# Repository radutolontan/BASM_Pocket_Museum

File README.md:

# Introduction

The Pocket Lab is the next-generation approach to science education. Designed by the Bucharest Applied STEAM Museum, it brings scientific exploration into anyone's hands. From citizen science projects to fearless exploration (guided or individual), the Pocket Lab illuminates the connections between Science, Technology, Engineering, Art, and Math in the world around us.

---

# Hardware Design

The system is built around an **ESP32-C6 MINI** microcontroller, which offers:
- Powerful processing capabilities
- WiFi and Bluetooth connectivity
- Excellent integration with accessible codebases through Arduino

The microcontroller collects data from a suite of sensors (9-DOF IMU, light, pressure, audio) and uses a chain of WS2812B RGB LEDs to relay measurements to the user. An on-board microSD card enables data logging and automated grading of student work. Everything is powered by a 3.7V LiPo cell, which is charged using the USB-C connector.
## Board ID - Education V0

### Power
The power stage is designed for a **500 mAh, 3.7V LiPo cell**. Key specifications:
- **Charger IC**: Configured to supply 450 mA in constant-current regime; stops charging when current drops below 150 mA in constant-voltage regime
- **USB-C Power**: Non-negotiated supply limited to 5V @ 500 mA (sufficient for system operation)
- **Voltage Monitor**: Prevents brown-out behavior on the ESP32 when the 3.3V rail drops below 2.9V
- **Power Latching**: A simple circuit enables and latches the LDO through push-button SW1 and an ESP32 GPIO 

### Display
The display consists of a chain of NeoPixel RGB LEDs organized across three zones:

**Mode Display (2 LEDs)** - Color-coded indication of the actively displayed quantity:
- WHITE → Light
- MAGENTA → Sound
- YELLOW → Magnetic Field
- GREEN → Acceleration
- ORANGE → Gyroscope
- RED → Air Temperature
- BLUE → Air Pressure

Additional device information is also displayed (e.g., battery state: Blinking Orange = Battery Low; Blinking Green = Charging; Blinking Blue = Fully Charged)

**Magnitude Display (3-4 LEDs)** - Conveys scalar quantities and magnitudes of vector quantities

**Direction Display (3 LEDs)** - Conveys qualitative Cartesian components (X, Y, Z) for vector quantities
- *Note: Direction Display is only available in Binary Display Mode (see Software Architecture section)*

### Sensors
The Pocket Lab EDU V0 includes the following sensors:

| Sensor | Measurements |
|--------|-------------|
| **ICM-20948** | 9-DOF IMU: translational acceleration, rotational velocity, magnetic field strength |
| **ICP-20100** | Ambient temperature and air pressure |
| **BH1750FVI** | Ambient light intensity |
| **MMICT390200012** | Microphone: sound pressure level (dB) |

### Programming
The MCU can be programmed through **Joint Download Boot Mode**:

1. Connect the Pocket Lab to a host computer using a USB-C data cable
2. Hold down **SW2** (labeled "MOD"; connected to GPIO 9)
3. While holding SW2, press and hold **SW1** (labeled "ON/OFF")
4. Release SW2 while keeping SW1 pressed
5. Release SW1

The USB-serial connection appears as `/dev/ttyACM*` (Linux) and allows PlatformIO to flash code to the ESP32-C6.

# Software Architecture

The software architecture is built around a FreeRTOS task-based design with a central `shared_data_buffer` for inter-task communication. Tasks are organized into two tiers:

## Task Organization

### First-Tier Tasks (Core System)
These tasks are **always active** and form the foundation of the Pocket Lab operation:
- **BMSTask** - Battery management and power control
- **SensorTask** - Sensor data acquisition and processing
- **AudioTask** - Audio input/output management
- **DisplayTask** - User interface via NeoPixel LEDs

### Application-Level Tasks (Feature-Specific)
These tasks are **conditionally enabled** based on active applications, demos, or features:
- **SDManager** - MicroSD card operations for data logging
- **EvaluatorTask** - Student performance assessment and grading
- **NetworkTask** - WiFi/Bluetooth connectivity features

## System Architecture Diagram

```mermaid
graph TB
    subgraph "First-Tier Tasks"
        BMS[BMSTask<br/>Power Management]
        SENSOR[SensorTask<br/>Data Acquisition]
        AUDIO[AudioTask<br/>Audio I/O]
        DISPLAY[DisplayTask<br/>Visual Feedback]
    end

    subgraph "Shared Memory"
        BUFFER[(SharedBuffer<br/>Circular Buffer)]
    end

    subgraph "Application Tasks"
        SD[SDManager]
        EVAL[EvaluatorTask]
        NET[NetworkTask]
    end

    BMS -->|Power Status| BUFFER
    SENSOR -->|Sensor Data| BUFFER
    AUDIO -->|Audio Data| BUFFER

    BUFFER -->|Latest Data| DISPLAY
    BUFFER -->|Historical Data| SD
    BUFFER -->|Statistics| EVAL
    BUFFER -->|Stream Data| NET

    BMS -.->|Shutdown Signal| SENSOR
    BMS -.->|Shutdown Signal| AUDIO
    BMS -.->|Shutdown Signal| DISPLAY

    DISPLAY -->|Mode Changes| BUFFER

    style BMS fill:#ffcccc
    style SENSOR fill:#ccffcc
    style AUDIO fill:#ccccff
    style DISPLAY fill:#ffffcc
    style BUFFER fill:#ffccff
```

## Detailed Task Descriptions
### 1. SensorTask
Responsible for initializing, managing, collecting, and processing sensor data. Pushes each new raw reading to the `shared_data_buffer`. Uses the **SensorHAL** virtual layer, as implemented in `specific_sensor_HAL`, to standardize high-level I/O across all sensors.

Furthermore, note that different sensors are sampled at different rates based on their response characteristics and application requirements.
The task maintains individual timers for each sensor and only reads when that sensor's interval has elapsed, optimizing power consumption and computational load.

#### States
* **BOOT** - Default state on boot-up; transition to INIT triggered from main.cpp
* **INIT** - Initializes I2C bus for communications to sensors, configures and confirms communications with all sensors
* **READ** - If a sensor is ready to read (based on its individual `read_rate_Hz`), captures a raw reading and commits it to the latest frame of `shared_data_buffer`

### 2. BMSTask
Responsible for managing power delivery to the Pocket Lab. Monitors battery health, informs user about remaining run-time, and handles power-up and shut-down of the entire system.

#### States
* **BOOT** - Waits until startup timer expires. Prevents accidental power-up if SW 1 is bumped.
* **STARTUP_LATCH** - Configures Charger IC monitoring pins after confirming power is latched.
* **ACTIVE** - Monitors feedback from the Charger IC & Battery Voltage predictions to infer ChargeControllerState:
    * **BATTERY_ONLY** - Charger unplugged & battery supplying power
    * **LOW_BATTERY** - Charger unplugged & battery supplying power & less than 30 minutes of battery life remaining
    * **CHARGING** - Charger connected & battery charging
    * **DONE_CHARGING** - Charger connected & supplying power to system (battery charging complete)
* **SHUTDOWN_PENDING** - When SW 1 is pressed to initiate a shut-down, the LDO is un-latched and other tasks are informed to facilitate a clean shut-down.

#### ⚠️ Known Critical Issues
The current BMSTask implementation has several critical issues that will be addressed in future revisions:
- **Limited voltage monitoring**: VBat is only checked when in `BATTERY_ONLY` state, missing voltage drops during charging or when connected to USB
- **No automatic low-voltage disconnect**: The system does not automatically disconnect power when VBat drops dangerously low, risking deep discharge that could trigger the battery's undervoltage lockout protection

### 3. AudioTask
Manages audio input and output operations for the Pocket Lab. The AudioTask is responsible for interfacing with the microphone sensor (MMICT390200012) and any future audio peripherals through a Hardware Abstraction Layer (HAL).
This decouples high-level audio processing from hardware-specific implementations, allowing to scale audio I/O in the future.
Like the SensorTask, the AudioTask writes processed audio data (e.g., sound pressure level in dB, frequency analysis) to the `shared_data_buffer`.

#### States
* **BOOT** - Default state on boot-up; transition to INIT triggered from main.cpp
* **INIT** - Initializes audio peripherals through the AudioHAL, configures sampling parameters
* **SAMPLING** - Actively captures audio data at the configured sample rate, processes it, and commits results to `shared_data_buffer`
* **IDLE** - Audio acquisition paused (e.g., during low-power modes or when no audio display is active)

### 4. DisplayTask
Manages the primary user feedback tool, the chain of NeoPixels. A push-button (SW 2 - display mode button) is debounced and used to cycle through DisplayStates. The current DisplayState is color-coded into the **Mode Display**.

#### States
* **BOOT** - Default state on boot-up; transition to INIT triggered from main.cpp
* **INIT** - Initializes the RGB LED strip and displays a color code for the GIT SHA (used to confirm proper code version is running)
* **DISPLAY_XX** - Pulls the latest value for the XX quantity from `shared_data_buffer`. Updates the **Magnitude Display** and **Mode Display** to reflect the measurement.

The DisplayTask supports two distinct visualization modes selected at boot time by holding (or not holding) the display mode button:

#### Visualization Modes - VU

VU mode provides a classic "volume unit" meter visualization reminiscent of analog audio equipment. In this mode, scalar measurements are displayed as a horizontal bar graph using 6 magnitude LEDs. The display shows the normalized percentage of the measurement relative to predefined min/max thresholds for each sensor type.

The magnitude LEDs use a gradient color scheme that transitions smoothly from green (low values) through yellow (mid-range) to red (high values), providing an intuitive visual indication of intensity. The more LEDs that are lit, the closer the measurement is to its maximum threshold. Vector quantities in VU mode display only their magnitude - no directional information is shown.

#### Visualization Modes - Binary (Integer Encoding)

Binary mode takes a fundamentally different approach by encoding the actual integer value of measurements rather than showing a percentage. This mode provides precise numerical information that can be decoded by reading the LED colors, making it particularly useful for debugging and data verification.

The system uses 4 magnitude LEDs to encode 12-bit values (0-4095) using a novel 3-bit-per-LED color encoding scheme:

**How Binary Encoding Works:**

Each RGB LED encodes 3 bits of information using its individual color channels:
- Blue channel = Bit m (LSB for that LED)
- Yellow channel = Bit m+1 (middle bit)
- Red channel = Bit m+2 (MSB for that LED)

The LEDs are arranged from left to right, with LED #1 (leftmost) showing bits 0-2, LED #2 showing bits 3-5, LED #3 showing bits 6-8, and LED #4 (rightmost) showing bits 9-11. This arrangement means that more LEDs being lit indicates a larger magnitude.

**Color Combinations:** The 3 bits per LED create 8 possible states (0-7), each displayed as a distinct color:
- `000` → OFF
- `001` → BLUE (bit 0 only)
- `010` → YELLOW (bit 1 only)
- `011` → GREEN (bits 0+1: blue+yellow = green)
- `100` → RED (bit 2 only)
- `101` → PURPLE (bits 0+2: blue+red = purple)
- `110` → ORANGE (bits 1+2: yellow+red = orange)
- `111` → WHITE (all three bits active)

**Example:** To encode the value 1059:
- 1059 in binary = `0100 0010 0011` = 2⁰ + 2¹ + 2⁵ + 2¹⁰
- LED #1 (bits 0-2 = `011`): Blue + Yellow = **GREEN**
- LED #2 (bits 3-5 = `100`): Red only = **RED**
- LED #3 (bits 6-8 = `000`): All off = **OFF**
- LED #4 (bits 9-11 = `100`): Red only = **RED**

Before encoding, sensor readings are multiplied by sensor-specific scaling factors (defined as `BINARY_MAG_ORDER_*` constants) to convert floating-point measurements into integer values. For example, temperature is multiplied by 10, so 25.3°C becomes 253, while pressure is multiplied by 10, converting 101.32 kPa to 1013 (then clamped to 4095). Note that acceleration and gyro measurements are very noisy and flicker significantly; the first two bits are masked, effectively rounding every measurement to a multiple of 4.

**Direction Display:**

Binary mode also displays vector components (X, Y, Z) using 3 dedicated direction LEDs. Each LED shows its component using a color gradient:
- **RED** → Negative values
- **OFF** → Near-zero values (±5% dead zone)
- **GREEN** → Positive values

The intensity of the color fades proportionally with the component's magnitude, providing both sign and strength information. 

## Application-Level Task Details

### 5. EvaluatorTask
Responsible for gauging user effort and measuring learning outcomes. The EvaluatorTask owns multiple instances of the abstract base class `EvaluatorBase`.

`EvaluatorBase` standardizes I/O across all evaluators, such as `DisplaySessionEvaluator` (which captures aggregate statistics on sensor data while a specific DisplayTask mode is active). This enables automated grading and feedback for educational activities.

#### States
* **BOOT** - Default state on boot-up; transition to INIT triggered from main.cpp
* **INIT** - Initializes and confirms appropriate logging is set up for all evaluators
* **RUNNING** - Checks progress on all evaluators and manages access to the SDManager queue for data logging
* **ERROR** - Error handling (not yet implemented)

### 6. SDManager
Owns operation of the microSD card. It manages access to the storage resource using a separate state machine, handling concurrent read/write requests from multiple tasks.

#### States
* **BOOT** - Default state on boot-up; transitions to INIT automatically after initializing SD queue
* **WAIT_FOR_INSERT** - Checks and debounces the state of the SD card detect GPIO
* **MOUNTING** - Starts SPI communications, mounts the SD card, and checks SD card metadata
* **READY** - Allows fulfillment of read/write requests in the queue
* **UNMOUNTING** - Unmounts the SD card if removal is detected
* **ERROR** - Error handling (not yet implemented)

### 7. NetworkTask
Manages WiFi and Bluetooth connectivity features. This task is enabled when network-based applications are active (e.g., data streaming, remote monitoring, firmware updates).

*Note: Full NetworkTask implementation details are under development.*

---

# SD Card Formatting

In order to read and write to the SD card, it must be formatted to **FAT32** with an **MBR** partition table.

## Formatting Instructions (Linux)

1. Insert the microSD card into a compatible card reader, connect to a Linux machine, and locate the device:
```bash
lsblk
```

2. Unmount any existing partitions and clear the card (replace `/dev/sdX` with your device):
```bash
sudo umount /dev/sdX*
sudo wipefs --all /dev/sdX
sudo fdisk /dev/sdX
```

3. Within `fdisk`, configure the following:
   - Press **`o`** → Create a new DOS (MBR) partition table
   - Press **`n`** → Create a new primary partition
   - Accept all defaults (press Enter)
   - Press **`t`**, then type **`c`** → Change partition type to W95 FAT32 (LBA)
   - Press **`w`** → Write changes and exit

4. Format the partition to FAT32:
```bash
sudo mkfs.vfat -F 32 -n SDCARD /dev/sdX1
```

The SD card is now ready for use with the Pocket Lab.

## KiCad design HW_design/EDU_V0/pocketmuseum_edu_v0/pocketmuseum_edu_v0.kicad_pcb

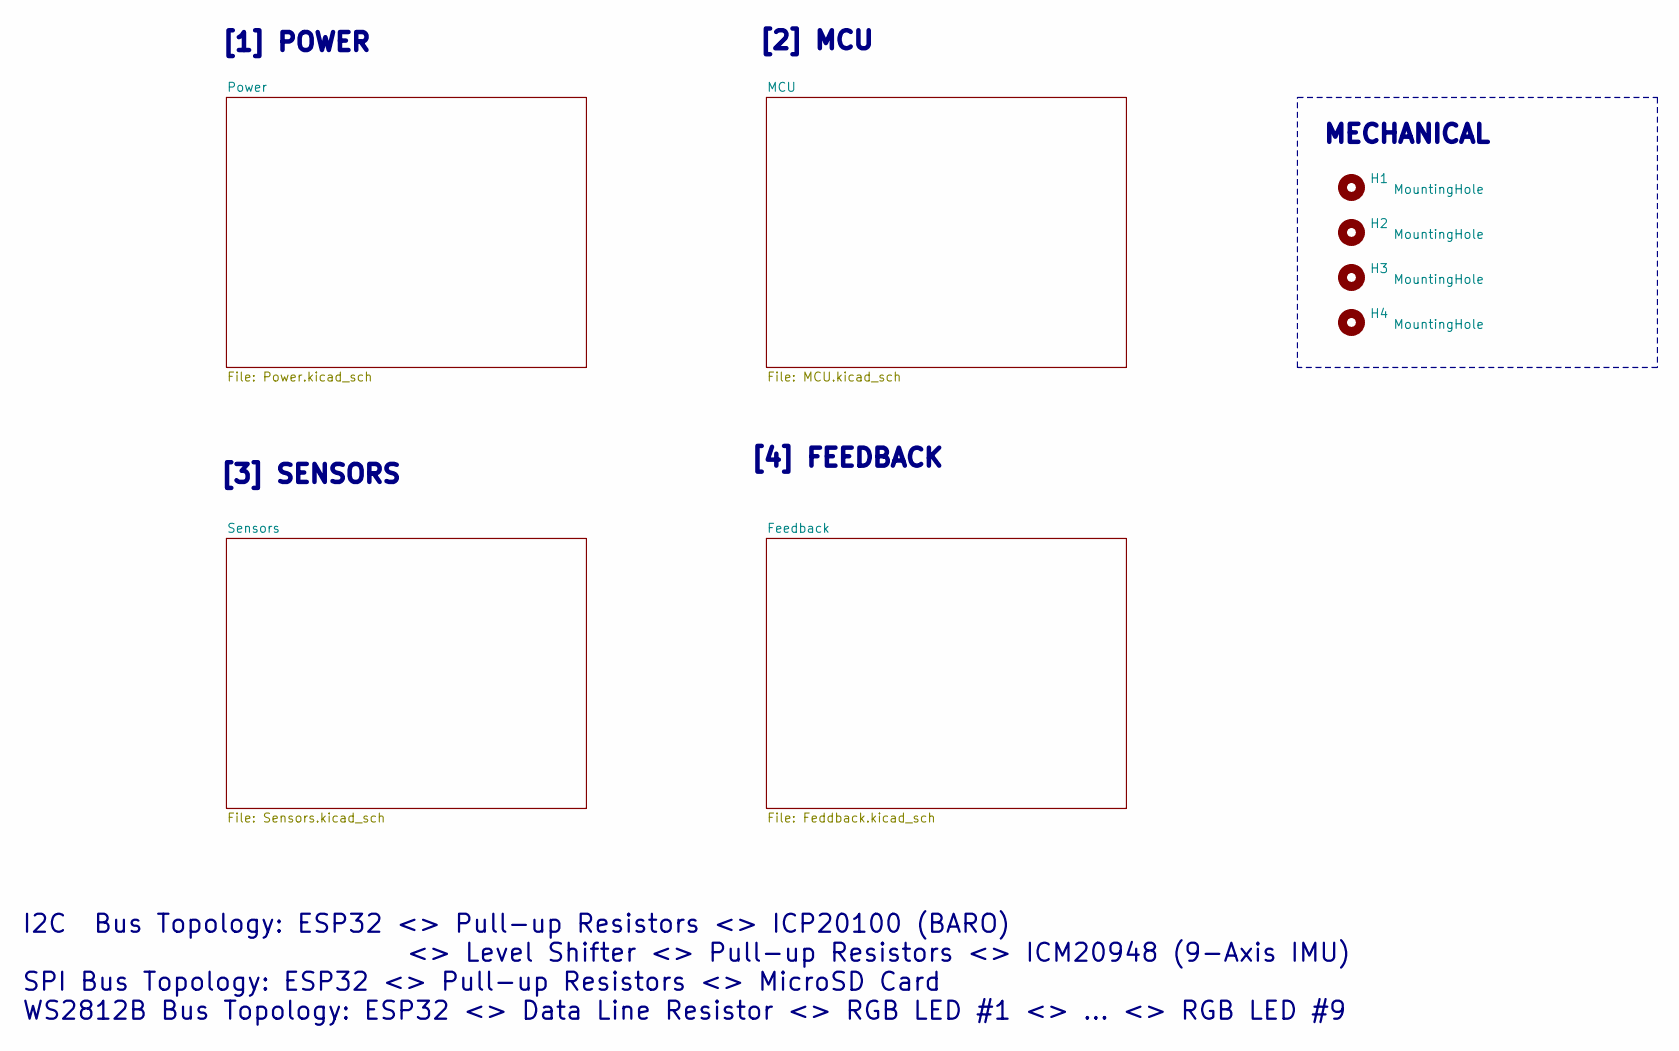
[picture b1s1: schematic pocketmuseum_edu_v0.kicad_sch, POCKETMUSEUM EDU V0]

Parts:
H1, H2, H3, H4: MountingHole; MountingHole_3.2mm_M3

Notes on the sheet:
[1] POWER
I2C Bus Topology: ESP32 <> Pull-up Resistors <> ICP20100 (BARO) <> Level Shifter <> Pull-up Resistors <> ICM20948 (9-Axis IMU) SPI Bus Topology: ESP32 <> Pull-up Resistors <> MicroSD Card WS2812B Bus Topology: ESP32 <> Data Line Resistor <> RGB LED #1 <> ... <> RGB LED #9
[2] MCU
[3] SENSORS
MECHANICAL
[4] FEEDBACK

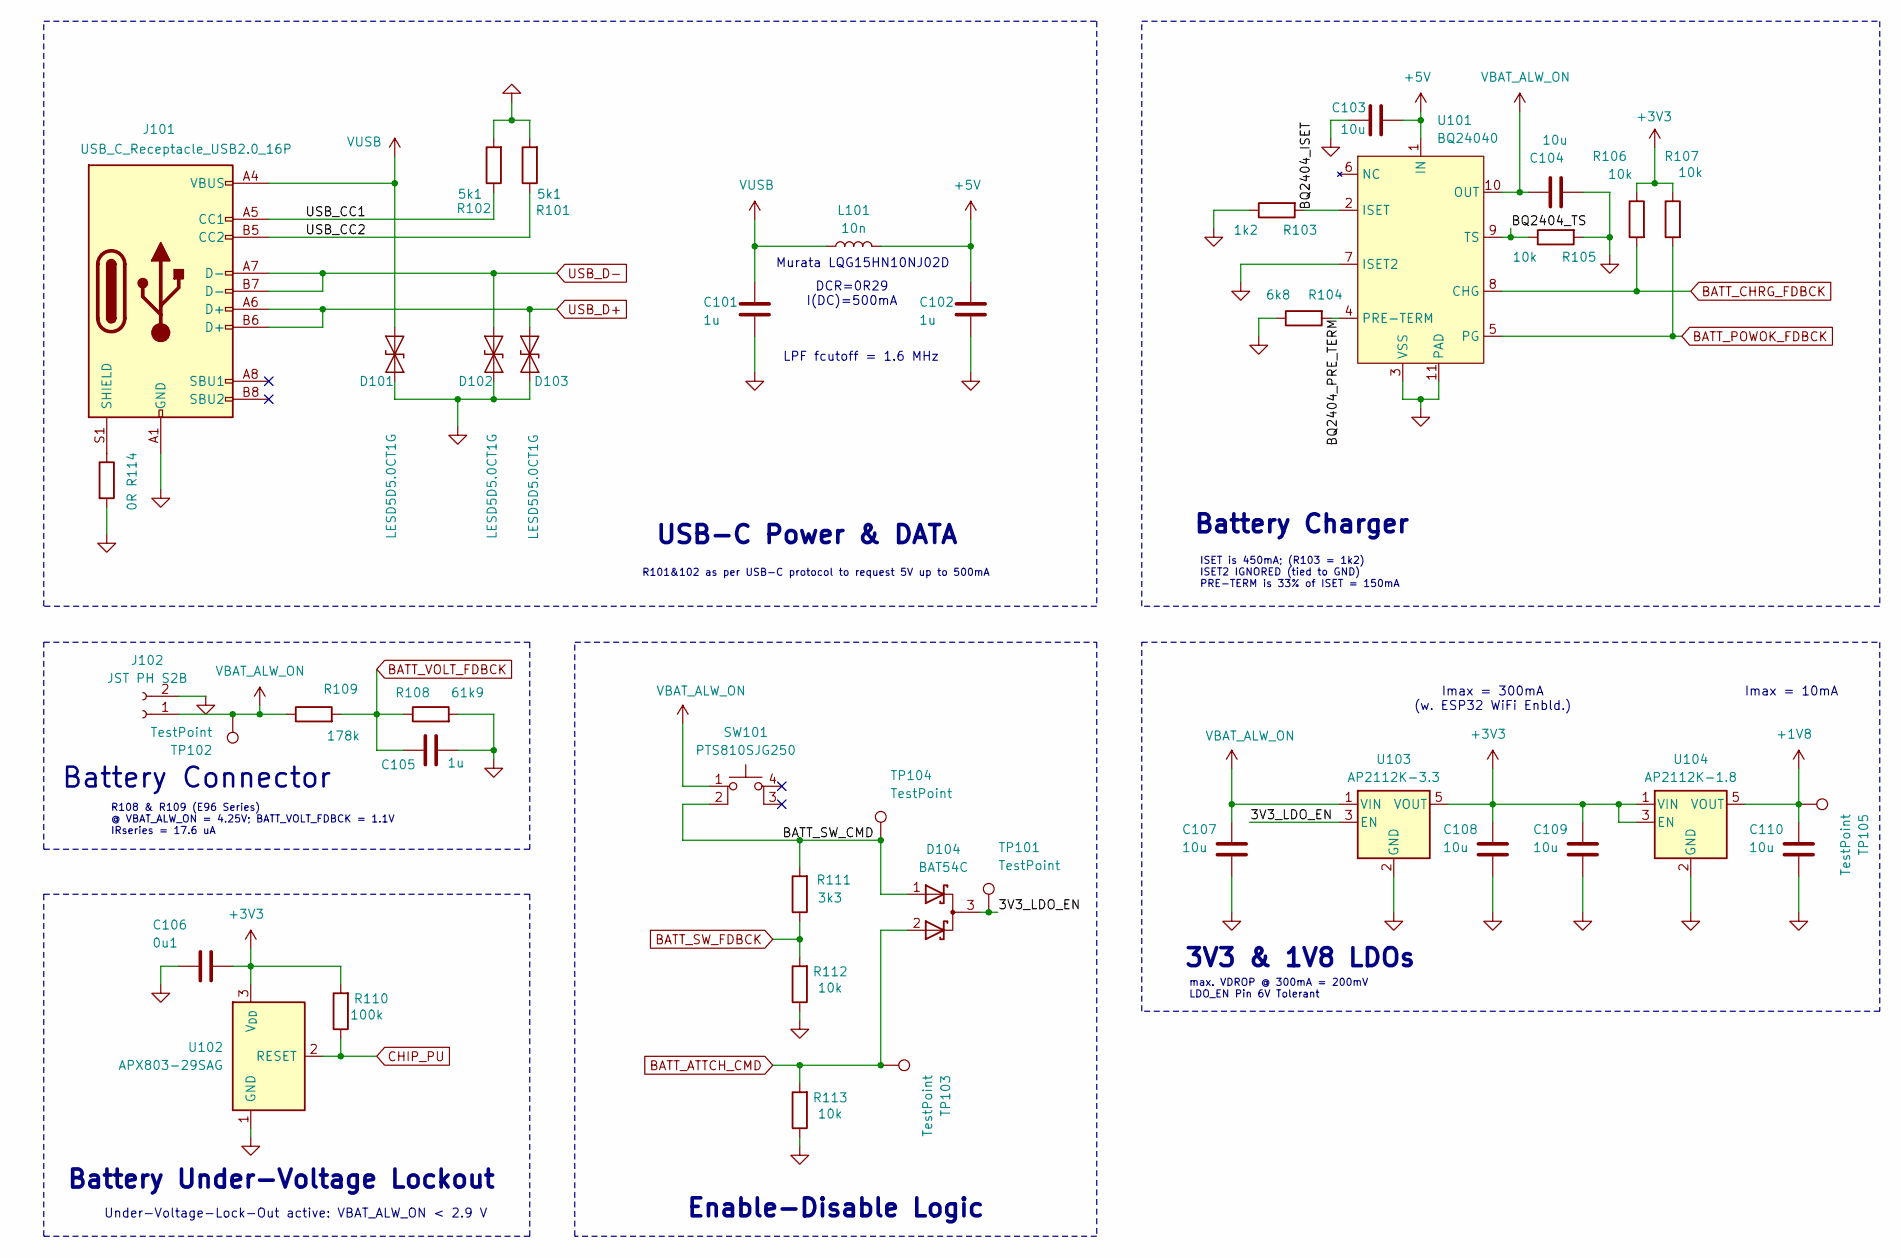
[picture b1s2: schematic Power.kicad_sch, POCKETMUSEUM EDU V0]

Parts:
C101, C102, C105: 1u; C_0402_1005Metric; Manufacturer P/N CL05A105KP5NNNC
C103, C104: 10u; C_0603_1608Metric; Manufacturer P/N CL05A105KP5NNNC
C106: 0u1; C_0402_1005Metric; Manufacturer P/N CL05A105KP5NNNC
C107, C108, C109, C110: 10u; C_0603_1608Metric; Manufacturer P/N CL10A226MQ8NRNC
D101, D102, D103: LESD5D5.0CT1G; D_SOD-523; Manufacturer P/N LESD5D5.0CT1G
D104: BAT54C; SOT-23
J101: USB_C_Receptacle_USB2.0_16P; USB_C_Receptacle_HRO_TYPE-C-31-M-12; Manufacturer P/N TYPE-C-31-M-12
J102: JST PH S2B; JST_PH_S2B-PH-SM4-TB_1x02-1MP_P2.00mm_Horizontal
L101: 10n; L_0402_1005Metric; Manufacturer P/N LQG15HS10NJ02D
R101, R102: 5k1; R_0402_1005Metric; Manufacturer P/N 0402WGF5101TCE
R103: 1k2; R_0402_1005Metric; Manufacturer P/N 0402WGF5101TCE
R104: 6k8; R_0402_1005Metric; Manufacturer P/N 0402WGF5101TCE
R105, R106, R107, R112, R113: 10k; R_0402_1005Metric; Manufacturer P/N 0402WGF5101TCE
R108: 61k9; R_0402_1005Metric; Manufacturer P/N 0402WGF5101TCE
R109: 178k; R_0402_1005Metric; Manufacturer P/N 0402WGF5101TCE
R110: 100k; R_0402_1005Metric; Manufacturer P/N 0402WGF5101TCE
R111: 3k3; R_0402_1005Metric; Manufacturer P/N 0402WGF5101TCE
R114: 0R; R_0603_1608Metric; Manufacturer P/N 0603WAJ0000T5E
SW101: PTS810SJG250; SW_SPST_PTS810
TP101, TP102, TP103, TP104, TP105: TestPoint; TestPoint_Pad_D2.0mm
U101: BQ24040; QFN_10_BQ24040
U102: APX803-29SAG; SOT-23
U103: AP2112K-3.3; SOT-23-5
U104: AP2112K-1.8; SOT-23-5

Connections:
+1V8: C110.1, TP105.1, U104.5 (VOUT); also elsewhere on the board
+3V3: C106.1, C108.1, C109.1, R106.1, R107.1, R110.2, U102.3 (V_{DD}), U103.5 (VOUT), U104.1 (VIN), U104.3 (EN); also elsewhere on the board
+5V: C102.1, C103.1, L101.2, U101.1 (IN)
/Power/3V3_LDO_EN: D104.3 (K), TP101.1, U103.3 (EN)
/Power/BATT_SW_CMD: D104.1 (A), R111.2, SW101.2, TP104.1
/Power/BQ2404_ISET: R103.2, U101.2 (ISET)
/Power/BQ2404_PRE_TERM: R104.2, U101.4 (PRE-TERM)
/Power/BQ2404_TS: R105.1, U101.9 (TS)
/Power/USB_CC1: J101.A5 (CC1), R102.1
/Power/USB_CC2: J101.B5 (CC2), R101.1
BATT_ATTCH_CMD: D104.2 (A), R113.2, TP103.1; also elsewhere on the board
BATT_CHRG_FDBCK: R106.2, U101.8 (CHG); also elsewhere on the board
BATT_POWOK_FDBCK: R107.2, U101.5 (PG); also elsewhere on the board
BATT_SW_FDBCK: R111.1, R112.2; also elsewhere on the board
BATT_VOLT_FDBCK: C105.1, R108.1, R109.2; also elsewhere on the board
CHIP_PU: R110.1, U102.2 (RESET); also elsewhere on the board
GND: C101.2, C102.2, C103.2, C104.2, C105.2, C106.2, C107.2, C108.2, C109.2, C110.2, D101.2 (A2), D102.2 (A2), D103.1 (A1), J101.A1 (GND), J101.A12 (GND), J101.B1 (GND), J101.B12 (GND), J102.2, R101.2, R102.2, R103.1, R104.1, R105.2, R108.2, R112.1, R113.1, R114.2, U101.3 (VSS), U101.7 (ISET2), U101.11 (PAD), U102.1 (GND), U103.2 (GND), U104.2 (GND); also elsewhere on the board
unnamed: J101.S1 (SHIELD), R114.1
USB_D+: D103.2 (A2), J101.A6 (D+), J101.B6 (D+); also elsewhere on the board
USB_D-: D102.1 (A1), J101.A7 (D-), J101.B7 (D-); also elsewhere on the board
VBAT_ALW_ON: C104.1, C107.1, J102.1, R109.1, SW101.1, TP102.1, U101.10 (OUT), U103.1 (VIN)
VUSB: C101.1, D101.1 (A1), J101.A4 (VBUS), J101.A9 (VBUS), J101.B4 (VBUS), J101.B9 (VBUS), L101.1

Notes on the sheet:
Murata LQG15HN10NJ02D
Under-Voltage-Lock-Out active: VBAT_ALW_ON < 2.9 V
Battery Connector
Imax = 300mA (w. ESP32 WiFi Enbld.)
ISET is 450mA; (R103 = 1k2) ISET2 IGNORED (tied to GND) PRE-TERM is 33% of ISET = 150mA
Battery Charger
DCR=0R29 I(DC)=500mA
USB-C Power & DATA
Battery Under-Voltage Lockout
R108 & R109 (E96 Series) @ VBAT_ALW_ON = 4.25V; BATT_VOLT_FDBCK = 1.1V IRseries = 17.6 uA
Enable-Disable Logic
max. VDROP @ 300mA = 200mV LDO_EN Pin 6V Tolerant
Imax = 10mA
LPF fcutoff = 1.6 MHz
3V3 & 1V8 LDOs
R101&102 as per USB-C protocol to request 5V up to 500mA

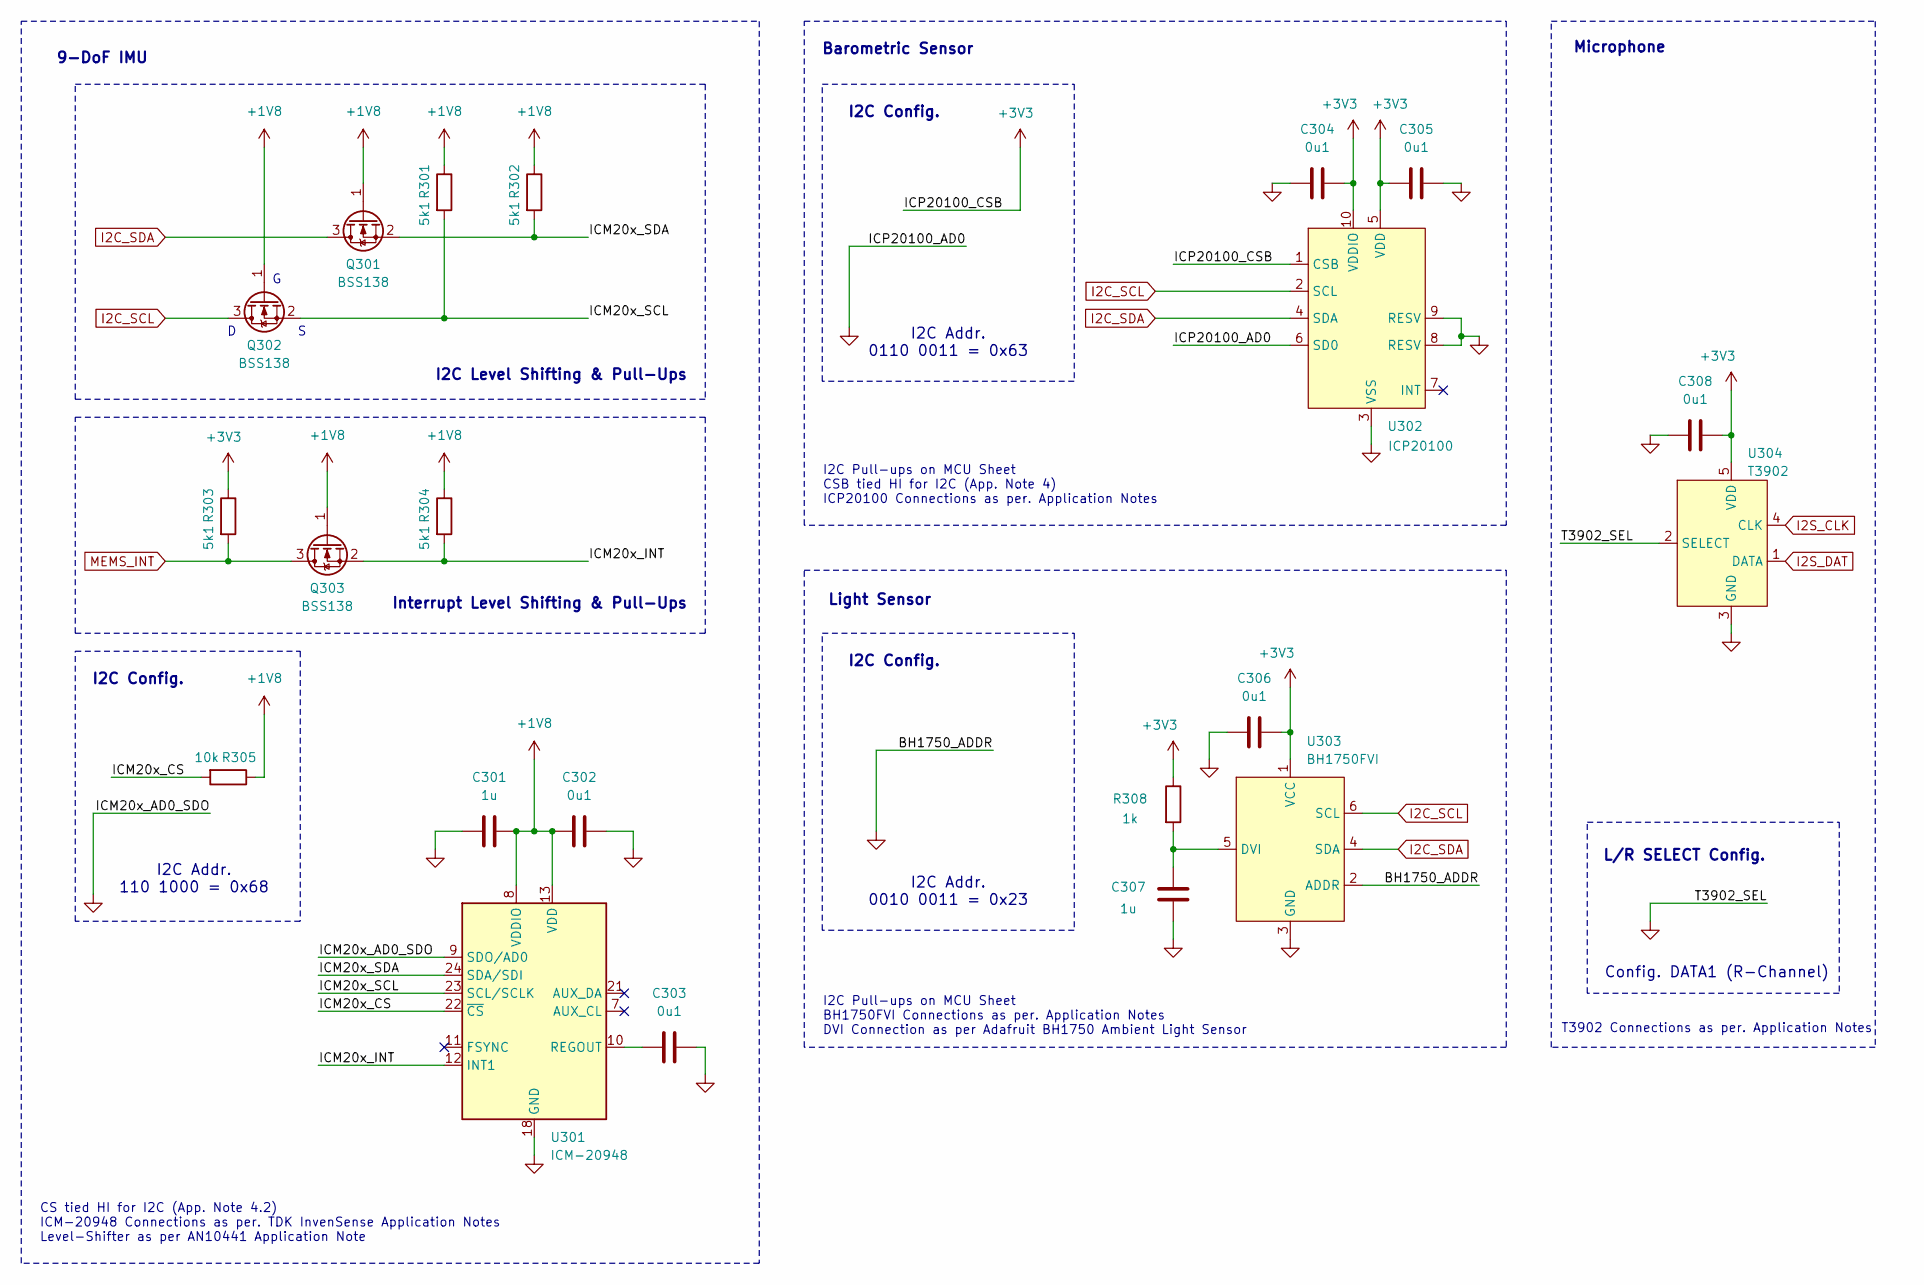
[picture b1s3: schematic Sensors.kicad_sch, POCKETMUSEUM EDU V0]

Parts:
C301, C307: 1u; C_0402_1005Metric; Manufacturer P/N CL05B104KO5NNNC
C302, C303, C304, C305, C306, C308: 0u1; C_0402_1005Metric; Manufacturer P/N CL05B104KO5NNNC
Q301, Q302, Q303: BSS138; SOT-23
R301, R302, R303, R304: 5k1; R_0402_1005Metric; Manufacturer P/N 0603WAJ0000T5E
R305: 10k; R_0402_1005Metric; Manufacturer P/N 0603WAJ0000T5E
R308: 1k; R_0402_1005Metric; Manufacturer P/N 0603WAJ0000T5E
U301: ICM-20948; InvenSense_QFN-24_3x3mm_P0.4mm
U302: ICP20100; ST_HLGA-10_2x2mm_P0.5mm_LayoutBorder3x2y; Manufacturer P/N ICP-20100
U303: BH1750FVI; XDCR_BH1750FVI-TR
U304: T3902; MMIC

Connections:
+1V8: C301.1, C302.2, Q301.1 (G), Q302.1 (G), Q303.1 (G), R301.1, R302.1, R304.1, R305.1, U301.8 (VDDIO), U301.13 (VDD); also elsewhere on the board
+3V3: C304.1, C305.2, C306.1, C308.1, R303.1, R308.1, U302.1 (CSB), U302.5 (VDD), U302.10 (VDDIO), U303.1 (VCC), U304.5 (VDD); also elsewhere on the board
/Sensors/ICM20x_CS: R305.2, U301.22 (~CS)
/Sensors/ICM20x_INT: Q303.2 (S), R304.2, U301.12 (INT1)
/Sensors/ICM20x_SCL: Q302.2 (S), R301.2, U301.23 (SCL/SCLK)
/Sensors/ICM20x_SDA: Q301.2 (S), R302.2, U301.24 (SDA/SDI)
GND: C301.2, C302.1, C303.1, C304.2, C305.1, C306.2, C307.2, C308.2, U301.9 (SDO/AD0), U301.18 (GND), U301.20 (GND), U302.3 (VSS), U302.6 (SD0), U302.8 (RESV), U302.9 (RESV), U303.2 (ADDR), U303.3 (GND), U304.2 (SELECT), U304.3 (GND); also elsewhere on the board
I2C_SCL: Q302.3 (D), U302.2 (SCL), U303.6 (SCL); also elsewhere on the board
I2C_SDA: Q301.3 (D), U302.4 (SDA), U303.4 (SDA); also elsewhere on the board
I2S_CLK: U304.4 (CLK); also elsewhere on the board
I2S_DAT: U304.1 (DATA); also elsewhere on the board
MEMS_INT: Q303.3 (D), R303.2; also elsewhere on the board
unnamed: C303.2, U301.10 (REGOUT)
unnamed: C307.1, R308.2, U303.5 (DVI)

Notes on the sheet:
I2C Pull-ups on MCU Sheet BH1750FVI Connections as per. Application Notes DVI Connection as per Adafruit BH1750 Ambient Light Sensor
I2C Pull-ups on MCU Sheet CSB tied HI for I2C (App. Note 4) ICP20100 Connections as per. Application Notes
T3902 Connections as per. Application Notes
I2C Config.
Microphone
I2C Addr. 0110 0011 = 0x63
I2C Addr. 110 1000 = 0x68
I2C Addr. 0010 0011 = 0x23
9-DoF IMU
Config. DATA1 (R-Channel)
Light Sensor
CS tied HI for I2C (App. Note 4.2) ICM-20948 Connections as per. TDK InvenSense Application Notes Level-Shifter as per AN10441 Application Note
I2C Level Shifting & Pull-Ups
Barometric Sensor
L/R SELECT Config.
Interrupt Level Shifting & Pull-Ups

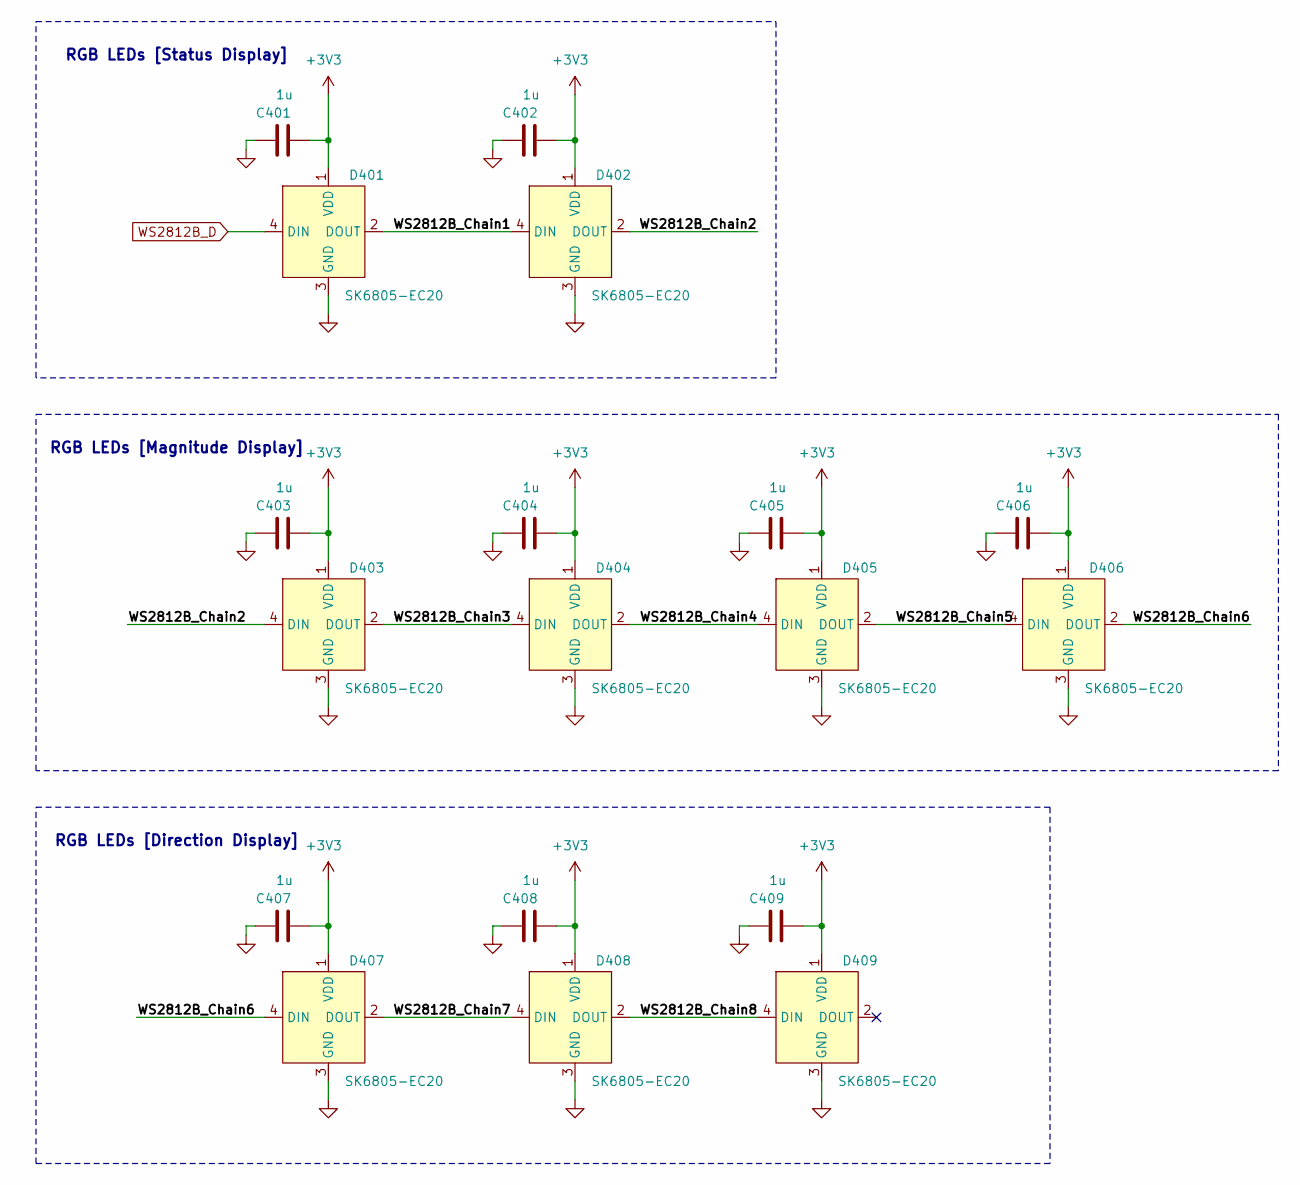
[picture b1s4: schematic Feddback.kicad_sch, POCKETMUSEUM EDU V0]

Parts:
C401, C402, C403, C404, C405, C406, C407, C408, C409: 1u; C_0402_1005Metric; Manufacturer P/N CL05A105KP5NNNC
D401, D402, D403, D404, D405, D406, D407, D408, D409: SK6805-EC20; SK68xx-EC20; Manufacturer P/N SK6805-EC20

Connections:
+3V3: C401.2, C402.2, C403.2, C404.2, C405.2, C406.2, C407.2, C408.2, C409.2, D401.1 (VDD), D402.1 (VDD), D403.1 (VDD), D404.1 (VDD), D405.1 (VDD), D406.1 (VDD), D407.1 (VDD), D408.1 (VDD), D409.1 (VDD); also elsewhere on the board
/Feedback/WS2812B_Chain1: D401.2 (DOUT), D402.4 (DIN)
/Feedback/WS2812B_Chain2: D402.2 (DOUT), D403.4 (DIN)
/Feedback/WS2812B_Chain3: D403.2 (DOUT), D404.4 (DIN)
/Feedback/WS2812B_Chain4: D404.2 (DOUT), D405.4 (DIN)
/Feedback/WS2812B_Chain5: D405.2 (DOUT), D406.4 (DIN)
/Feedback/WS2812B_Chain6: D406.2 (DOUT), D407.4 (DIN)
/Feedback/WS2812B_Chain7: D407.2 (DOUT), D408.4 (DIN)
/Feedback/WS2812B_Chain8: D408.2 (DOUT), D409.4 (DIN)
GND: C401.1, C402.1, C403.1, C404.1, C405.1, C406.1, C407.1, C408.1, C409.1, D401.3 (GND), D402.3 (GND), D403.3 (GND), D404.3 (GND), D405.3 (GND), D406.3 (GND), D407.3 (GND), D408.3 (GND), D409.3 (GND); also elsewhere on the board
WS2812B_D: D401.4 (DIN); also elsewhere on the board

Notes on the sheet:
RGB LEDs [Magnitude Display]
RGB LEDs [Direction Display]
RGB LEDs [Status Display]

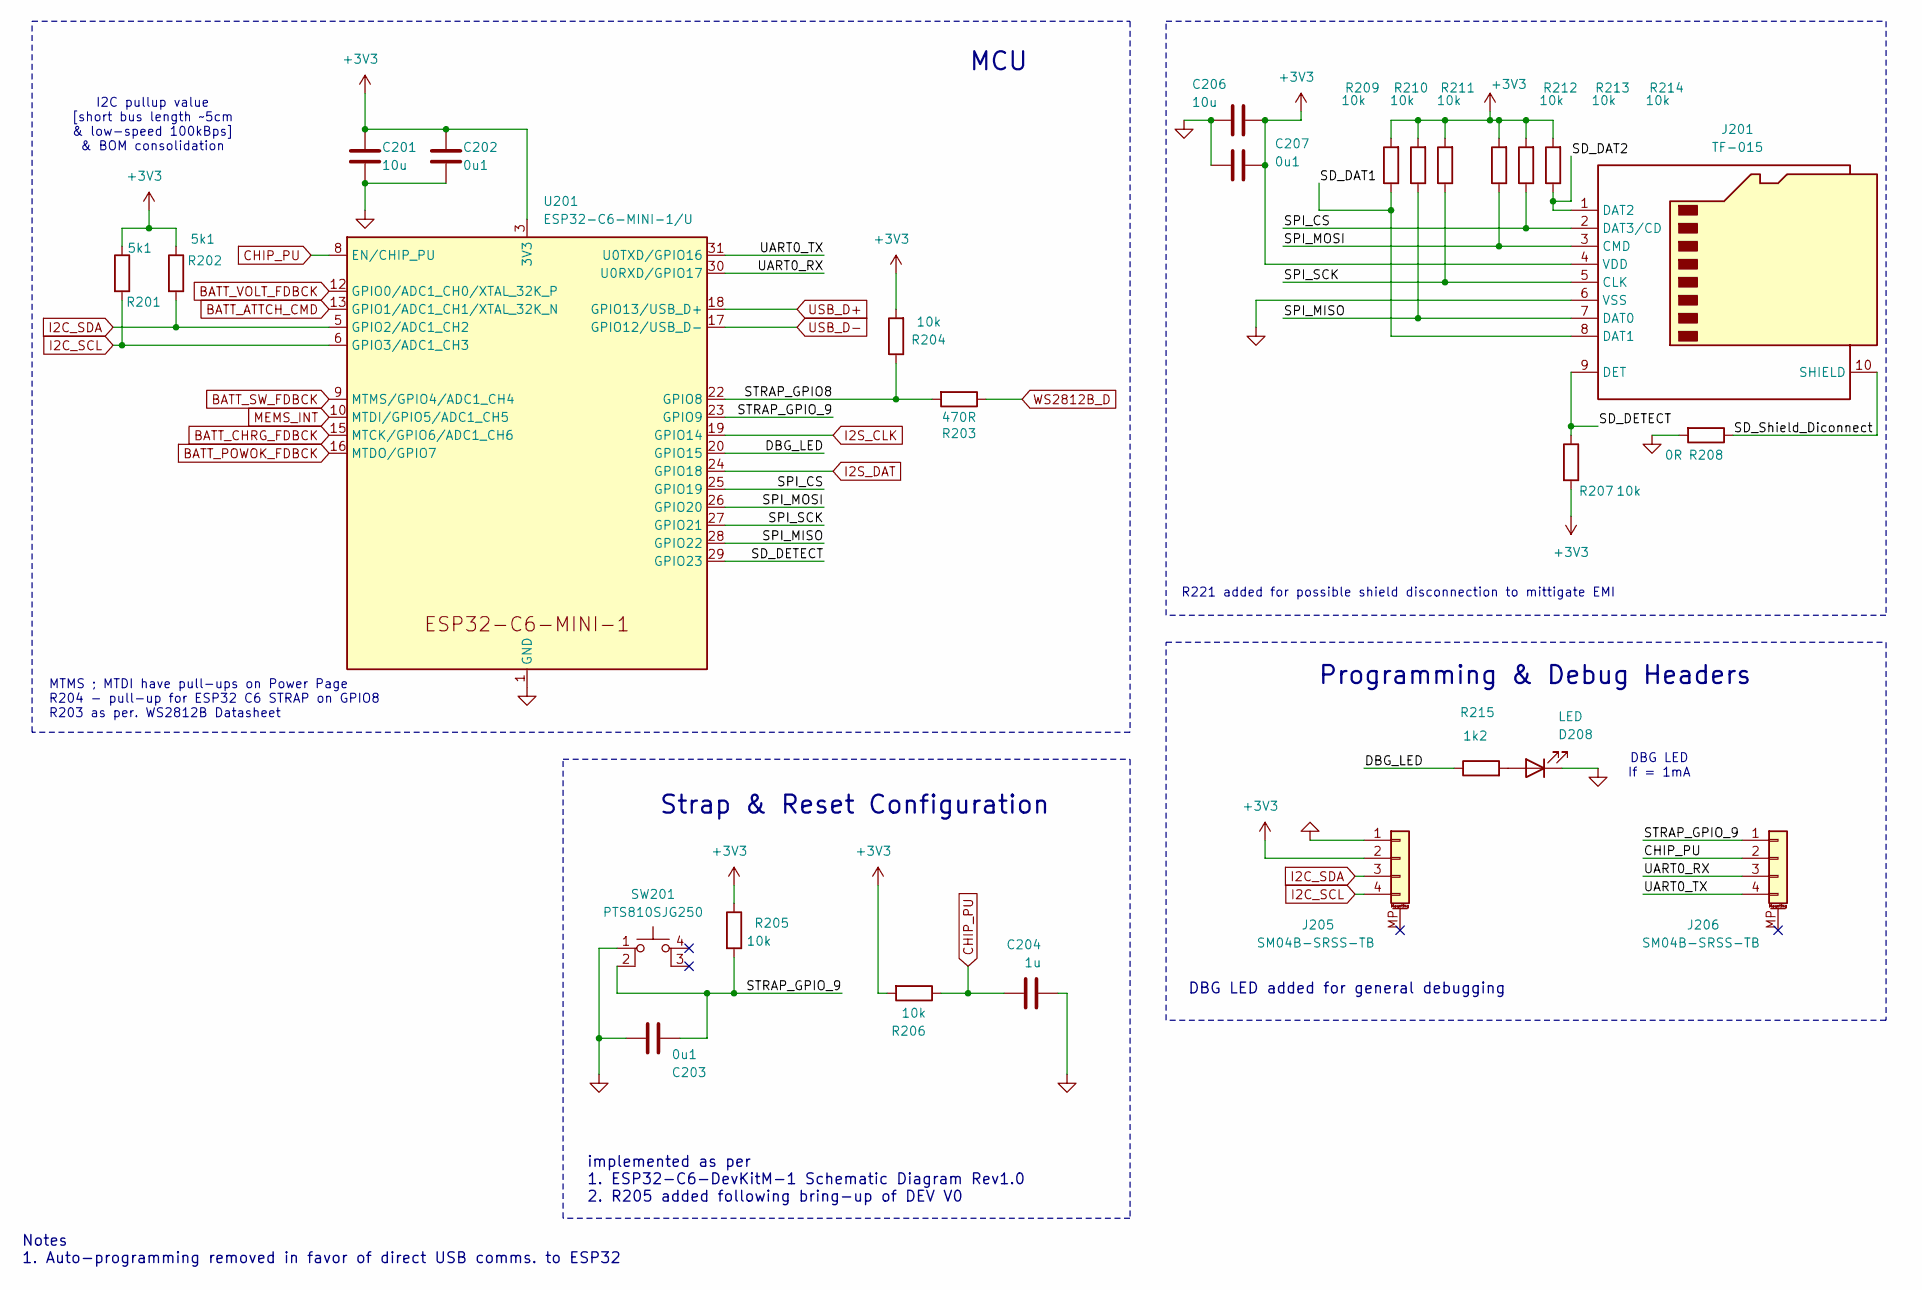
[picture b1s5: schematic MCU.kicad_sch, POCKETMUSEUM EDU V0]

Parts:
C201, C206: 10u; C_0603_1608Metric; Manufacturer P/N CL10A106MQ8NNNC
C202, C203, C207: 0u1; C_0402_1005Metric; Manufacturer P/N CL05B104KO5NNNC
C204: 1u; C_0402_1005Metric; Manufacturer P/N CL05A105KP5NNNC
D208: LED; LED_0402_1005Metric; Manufacturer P/N YLED0402R
J201: TF-015; TF-015_SOFNG
J205, J206: SM04B-SRSS-TB; JST_SH_SM04B-SRSS-TB_1x04-1MP_P1.00mm_Horizontal; Manufacturer P/N BM04B-SRSS-TB(LF)(SN)
R201, R202: 5k1; R_0402_1005Metric; Manufacturer P/N 0402WGF5101TCE
R203: 470R; R_0402_1005Metric; Manufacturer P/N 0402WGF4700TCE
R204, R205, R206, R207, R209, R210, R211, R212, R213, R214: 10k; R_0402_1005Metric; Manufacturer P/N 0402WGF1002TCE
R208: 0R; R_0603_1608Metric; Manufacturer P/N 0603WAJ0000T5E
R215: 1k2; R_0402_1005Metric; Manufacturer P/N 0402WGF2001TCE
SW201: PTS810SJG250; SW_SPST_PTS810
U201: ESP32-C6-MINI-1/U; ESP32-C6-MINI-1; Manufacturer P/N ESP32-C6-MINI-1-N4

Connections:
+3V3: C201.1, C202.1, C206.1, C207.1, J201.4 (VDD), J205.2, R201.1, R202.1, R204.2, R205.1, R206.2, R207.2, R209.2, R210.2, R211.2, R212.2, R213.2, R214.2, U201.3 (3V3); also elsewhere on the board
/MCU/DBG_LED: R215.1, U201.20 (GPIO15)
/MCU/SD_DAT1: J201.8 (DAT1), R209.1
/MCU/SD_DAT2: J201.1 (DAT2), R214.1
/MCU/SD_DETECT: J201.9 (DET), R207.1, U201.29 (GPIO23)
/MCU/SD_Shield_Diconnect: J201.10 (SHIELD), R208.1
/MCU/SPI_CS: J201.2 (DAT3/CD), R213.1, U201.25 (GPIO19)
/MCU/SPI_MISO: J201.7 (DAT0), R210.1, U201.28 (GPIO22)
/MCU/SPI_MOSI: J201.3 (CMD), R212.1, U201.26 (GPIO20)
/MCU/SPI_SCK: J201.5 (CLK), R211.1, U201.27 (GPIO21)
/MCU/STRAP_GPIO8: R203.2, R204.1, U201.22 (GPIO8)
/MCU/STRAP_GPIO_9: C203.1, J206.1, R205.2, SW201.2, U201.23 (GPIO9)
/MCU/UART0_RX: J206.3, U201.30 (U0RXD/GPIO17)
/MCU/UART0_TX: J206.4, U201.31 (U0TXD/GPIO16)
BATT_ATTCH_CMD: U201.13 (GPIO1/ADC1_CH1/XTAL_32K_N); also elsewhere on the board
BATT_CHRG_FDBCK: U201.15 (MTCK/GPIO6/ADC1_CH6); also elsewhere on the board
BATT_POWOK_FDBCK: U201.16 (MTDO/GPIO7); also elsewhere on the board
BATT_SW_FDBCK: U201.9 (MTMS/GPIO4/ADC1_CH4); also elsewhere on the board
BATT_VOLT_FDBCK: U201.12 (GPIO0/ADC1_CH0/XTAL_32K_P); also elsewhere on the board
CHIP_PU: C204.1, J206.2, R206.1, U201.8 (EN/CHIP_PU); also elsewhere on the board
GND: C201.2, C202.2, C203.2, C204.2, C206.2, C207.2, D208.1 (K), J201.6 (VSS), J205.1, R208.2, SW201.1, U201.1 (GND), U201.2 (GND), U201.11 (GND), U201.14 (GND), U201.36 (GND), U201.37 (GND), U201.38 (GND), U201.39 (GND), U201.40 (GND), U201.41 (GND), U201.42 (GND), U201.43 (GND), U201.44 (GND), U201.45 (GND), U201.46 (GND), U201.47 (GND), U201.48 (GND), U201.49 (GND), U201.50 (GND), U201.51 (GND), U201.52 (GND), U201.53 (GND); also elsewhere on the board
I2C_SCL: J205.4, R201.2, U201.6 (GPIO3/ADC1_CH3); also elsewhere on the board
I2C_SDA: J205.3, R202.2, U201.5 (GPIO2/ADC1_CH2); also elsewhere on the board
I2S_CLK: U201.19 (GPIO14); also elsewhere on the board
I2S_DAT: U201.24 (GPIO18); also elsewhere on the board
MEMS_INT: U201.10 (MTDI/GPIO5/ADC1_CH5); also elsewhere on the board
unnamed: D208.2 (A), R215.2
USB_D+: U201.18 (GPIO13/USB_D+); also elsewhere on the board
USB_D-: U201.17 (GPIO12/USB_D-); also elsewhere on the board
WS2812B_D: R203.1; also elsewhere on the board

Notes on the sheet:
DBG LED If = 1mA
DBG LED added for general debugging
Programming & Debug Headers
R221 added for possible shield disconnection to mittigate EMI
implemented as per 1. ESP32-C6-DevKitM-1 Schematic Diagram Rev1.0 2. R205 added following bring-up of DEV V0
Strap & Reset Configuration
MTMS ; MTDI have pull-ups on Power Page R204 - pull-up for ESP32 C6 STRAP on GPIO8 R203 as per. WS2812B Datasheet
I2C pullup value [short bus length ~5cm & low-speed 100kBps] & BOM consolidation
MCU
Notes 1. Auto-programming removed in favor of direct USB comms. to ESP32
